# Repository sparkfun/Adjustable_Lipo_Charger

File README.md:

SparkFun Adjustable LiPo Charger
============================================

[*Adjustable LiPo Charger (PRT-14380)*](https://www.sparkfun.com/products/14380)

The Adjustable LiPo Charger will charge any single cell Lithium Ion (Li-Ion) or Lithium Polymer (LiPo) battery with a maximum current of 500mA. Simply plug in a micro B USB cable or any power supply between 3.75-6VDC to one end, and your rechargeable lithium battery to the other end. Once the current has been set on the DIP switches you're ready to go to charge your battery in 100mA increments up to 500mA, or as low as 15mA using the custom charge rate by soldering in the appropriate resistor to R_PTH.

Repository Contents
-------------------

* **/Hardware** - All Eagle design files (.brd and .sch)
* **/Production** - Production panel files

Documentation
-------------------

* [Adjustable LiPo Charger Hookup Guide ](https://learn.sparkfun.com/tutorials/adjustable-lipo-charger-hookup-guide)

License Information
-------------------
This product is _**open source**_! 

Please review the LICENSE.md file for license information. 

If you have any questions or concerns on licensing, please contact techsupport@sparkfun.com.

Distributed as-is; no warranty is given.

- Your friends at SparkFun.

All other code is open source so please feel free to do anything you want with it; you buy me a beer if you use this and we meet someday ([Beerware license](http://en.wikipedia.org/wiki/Beerware)).

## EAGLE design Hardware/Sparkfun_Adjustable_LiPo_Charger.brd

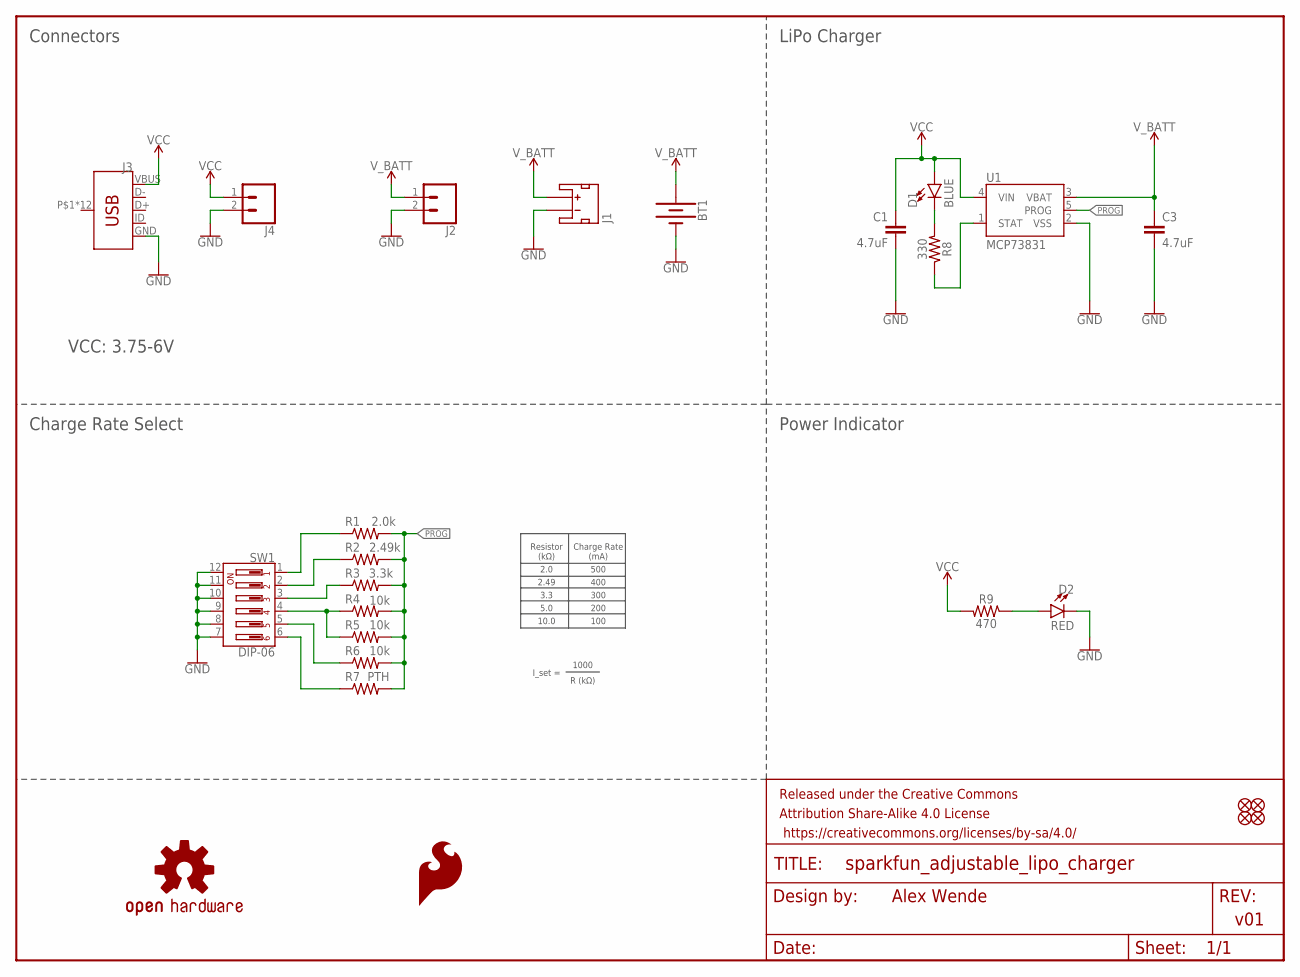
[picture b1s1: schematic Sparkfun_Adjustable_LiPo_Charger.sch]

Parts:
BT1: BATTERY-24.5MM_SMD; BATTCON_24.5MM_SMD
C1, C3: 4.7uF; 0603
D1: BLUE; LED-0603
D2: RED; LED-0603
FD1, FD2, FD3, FD4: FIDUCIALUFIDUCIAL; FIDUCIAL-MICRO
FRAME1: FRAME-LETTER; CREATIVE_COMMONS
J1: JST_2MM_MALE; JST-2-SMD
J2, J4: CONN_021X02_NO_SILK; 1X02_NO_SILK
J3: USB_MICRO-B_HALF_PTH; USB-MICROB-PTH
LOGO1: SFE_LOGO_FLAME.1_INCH; SFE_LOGO_FLAME_.1
LOGO2: OSHW-LOGOS; OSHW-LOGO-S
R1: 2.0k; 0603
R2: 2.49k; 0603
R3: 3.3k; 0603
R4, R5, R6: 10k; 0603
R7: PTH; AXIAL-0.3
R8: 330; 0603
R9: 470; 0603
SW1: DIP-06; DIPSWITCH-06-SMD
U1: MCP73831; SOT23-5

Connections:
GND: BT1.2 (-), C1.2, C3.2, D2.C, J1.1 (-), J2.2, J3.GND, J4.2, SW1.7, SW1.8, SW1.9, SW1.10, SW1.11, SW1.12, U1.2 (VSS)
unnamed: R8.1, U1.1 (STAT)
unnamed: R1.1, SW1.1
unnamed: R2.1, SW1.2
unnamed: R3.1, SW1.3
unnamed: R4.1, R5.1, SW1.4
unnamed: R6.1, SW1.5
unnamed: R7.P$1 (1), SW1.6
unnamed: D1.C, R8.2
unnamed: D2.A, R9.1
PROG: R1.2, R2.2, R3.2, R4.2, R5.2, R6.2, R7.P$2 (2), U1.5 (PROG)
VCC: C1.1, D1.A, J3.VBUS, J4.1, R9.2, U1.4 (VIN)
V_BATT: BT1.3 (+), C3.1, J1.2 (+), J2.1, U1.3 (VBAT)

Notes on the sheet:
Alex Wende
v01
Connectors
Charge Rate Select
Resistor (kΩ)
Charge Rate (mA)
2.0
2.49
3.3
5.0
10.0
500
400
300
200
100
I_set =
1000
R (kΩ)
LiPo Charger
VCC: 3.75-6V
Power Indicator

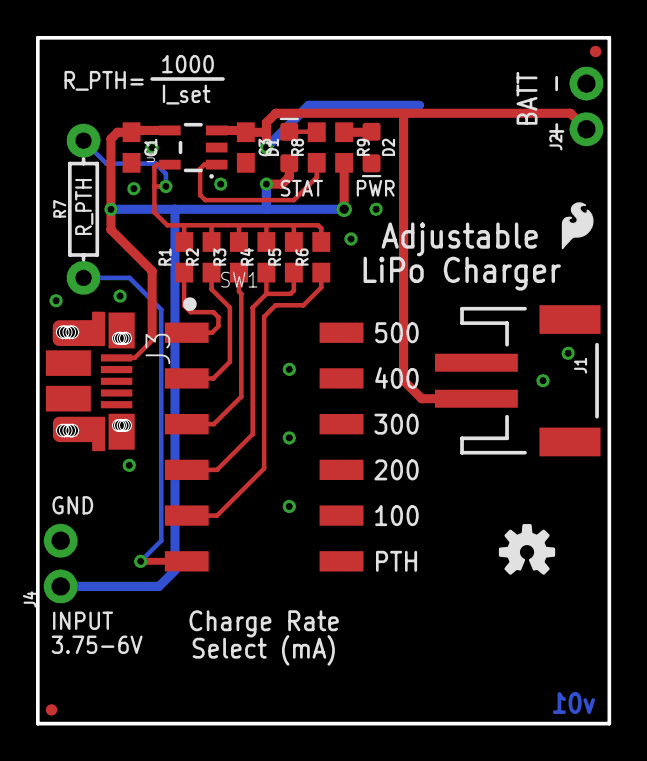
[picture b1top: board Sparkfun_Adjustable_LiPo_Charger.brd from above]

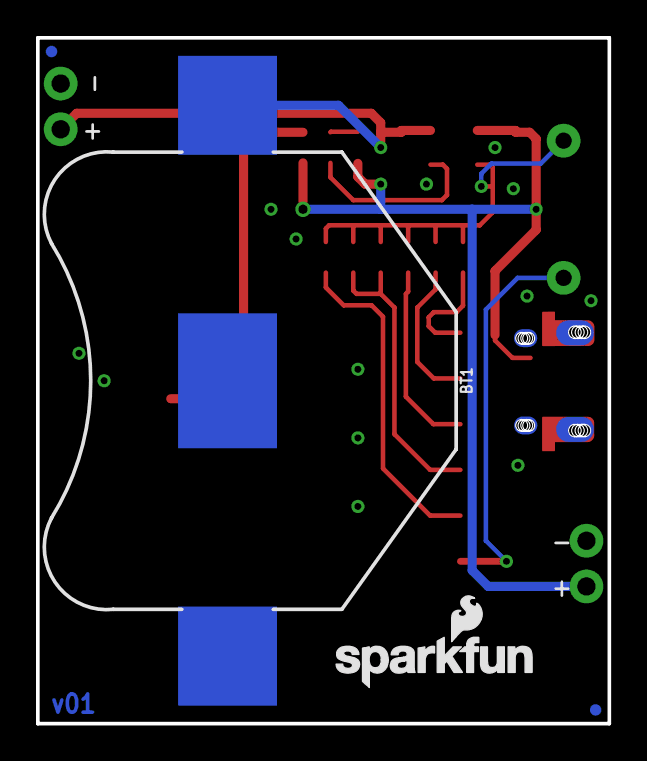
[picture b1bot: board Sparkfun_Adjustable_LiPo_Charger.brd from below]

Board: 2 copper layers, 31.8 x 38.1 mm, 28 parts (4 on the bottom side), 13 nets.

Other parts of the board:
U$1: SFE_LOGO_NAME_FLAME_.1

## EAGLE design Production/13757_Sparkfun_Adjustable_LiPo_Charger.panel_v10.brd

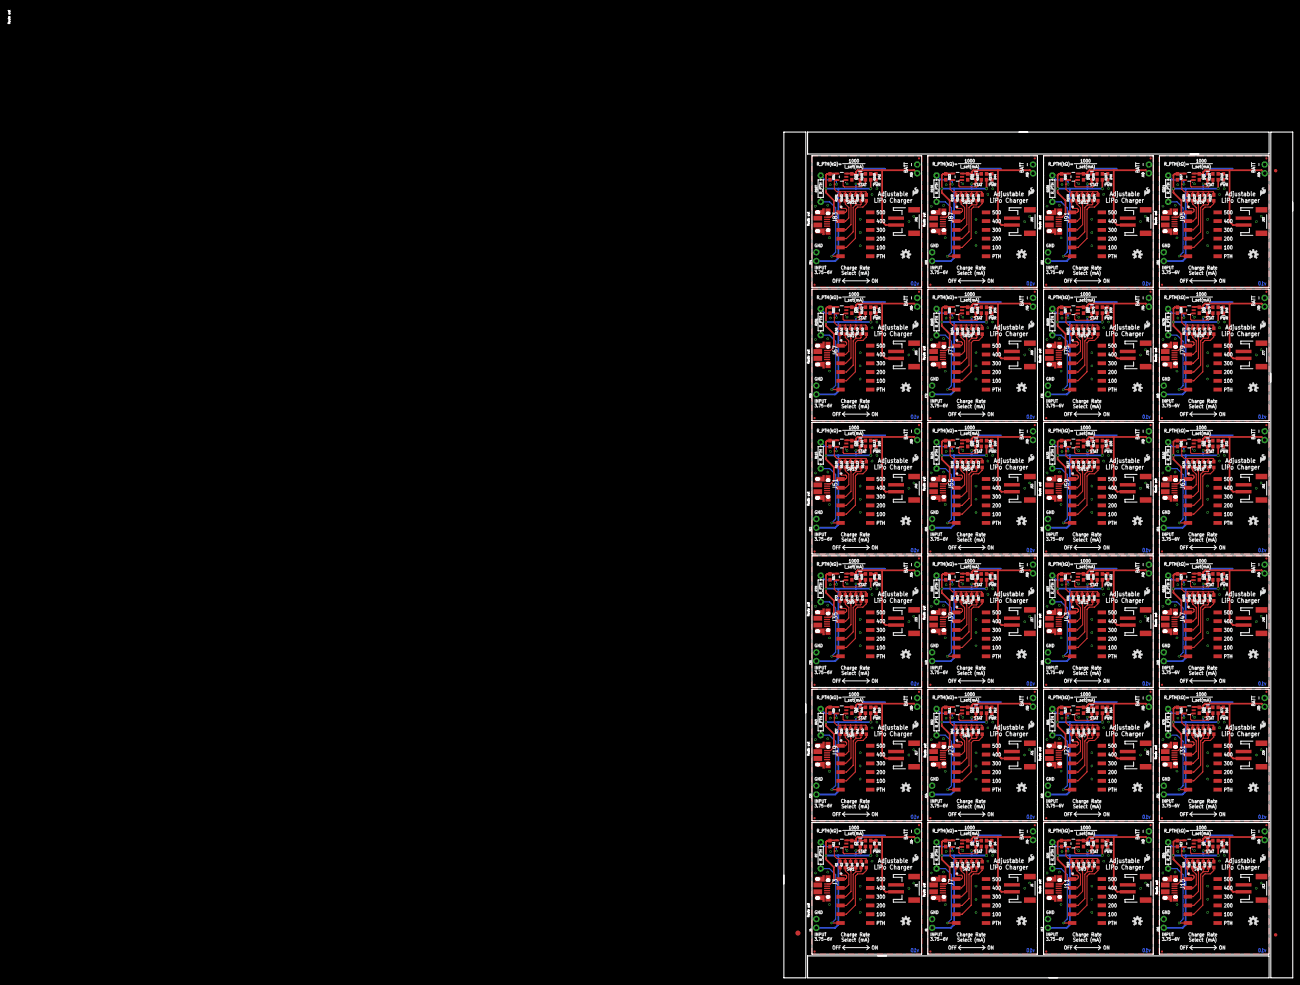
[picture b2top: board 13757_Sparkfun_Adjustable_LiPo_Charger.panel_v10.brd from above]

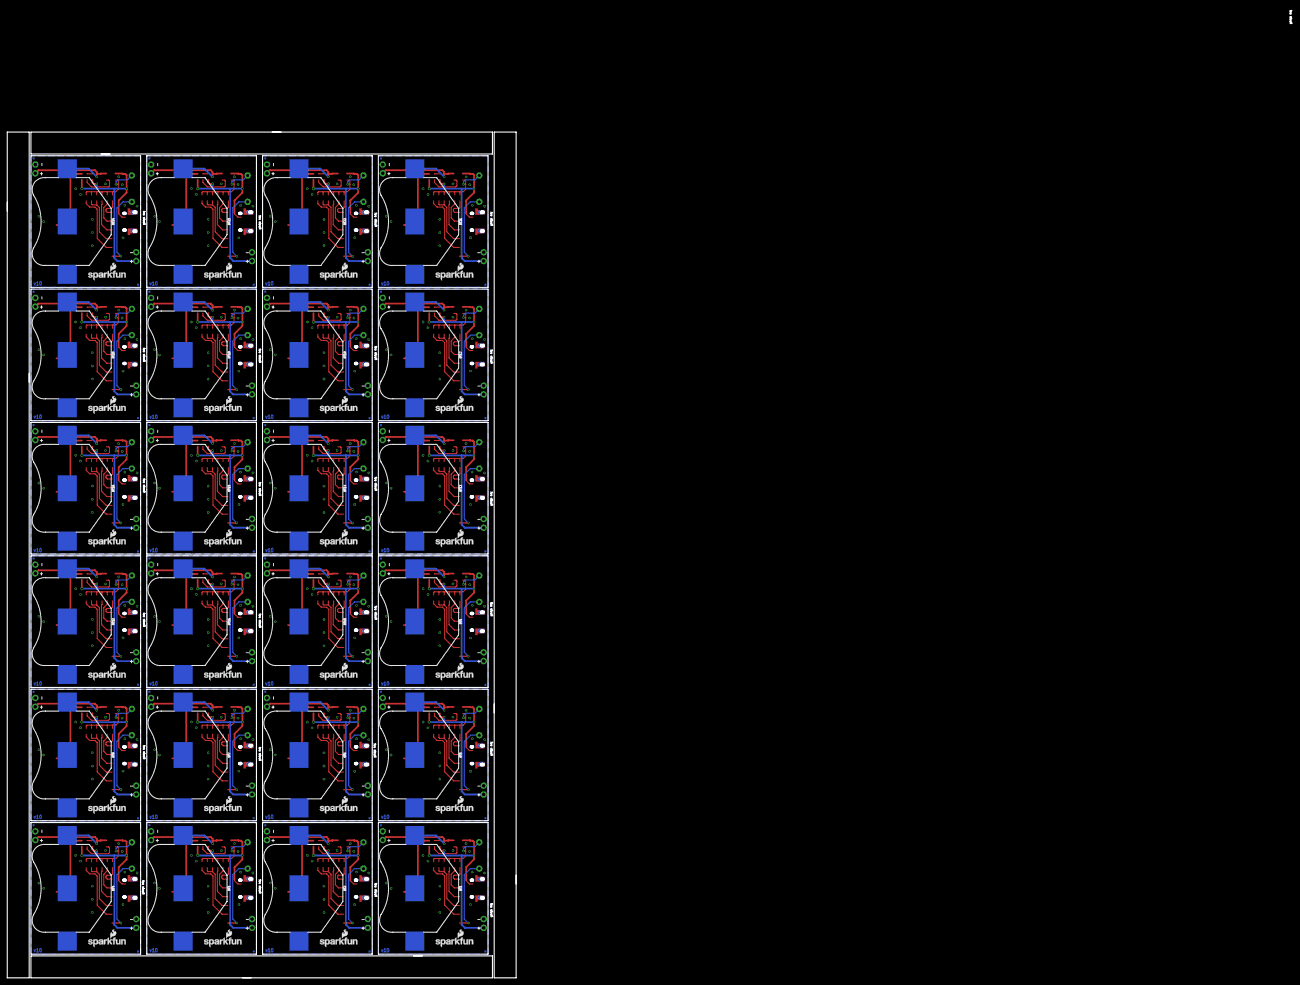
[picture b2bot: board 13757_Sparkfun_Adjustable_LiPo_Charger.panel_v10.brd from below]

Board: 2 copper layers, 372.2 x 281.0 mm, 651 parts (96 on the bottom side), 312 nets.

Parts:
BT1, BT2, BT3, BT4, BT5, BT6, BT7, BT8, BT9, BT10, BT11, BT12, BT13, BT14, BT15, BT16, BT17, BT18, BT19, BT20, BT21, BT22, BT23, BT24: BATTCON_24.5MM_SMD
C1, C2, C3, C4, C5, C6, C7, C8, C9, C10, C11, C12, C13, C14, C15, C16, C17, C18, C19, C20, C21, C22, C23, C24, C25, C26, C27, C28, C29, C30, C31, C32, C33, C34, C35, C36, C37, C38, C39, C40, C41, C42, C43, C44, C45, C46, C47, C48: 4.7uF; 0603
D1, D3, D5, D7, D9, D11, D13, D15, D17, D19, D21, D23, D25, D27, D29, D31, D33, D35, D37, D39, D41, D43, D45, D47: BLUE; LED-0603
D2, D4, D6, D8, D10, D12, D14, D16, D18, D20, D22, D24, D26, D28, D30, D32, D34, D36, D38, D40, D42, D44, D46, D48: RED; LED-0603
E$1: FIDUCIAL-1.5X3
E$7, E$8: FIDUCIAL-1X2
FD1, FD2, FD3, FD4, FD5, FD6, FD7, FD8, FD9, FD10, FD11, FD12, FD13, FD14, FD15, FD16, FD17, FD18, FD19, FD20, FD21, FD22, FD23, FD24, FD25, FD26, FD27, FD28, FD29, FD30, FD31, FD32, FD33, FD34, FD35, FD36, FD37, FD38, FD39, FD40, FD41, FD42, FD43, FD44, FD45, FD46, FD47, FD48, FD49, FD50, FD51, FD52, FD53, FD54, FD55, FD56, FD57, FD58, FD59, FD60, FD61, FD62, FD63, FD64, FD65, FD66, FD67, FD68, FD69, FD70, FD71, FD72, FD73, FD74, FD75, FD76, FD77, FD78, FD79, FD80, FD81, FD82, FD83, FD84, FD85, FD86, FD87, FD88, FD89, FD90, FD91, FD92, FD93, FD94, FD95, FD96: FIDUCIALUFIDUCIAL; FIDUCIAL-MICRO
J1, J5, J9, J13, J17, J21, J25, J29, J33, J37, J41, J45, J49, J53, J57, J61, J65, J69, J73, J77, J81, J85, J89, J93: JST-2-SMD
J2, J4, J6, J8, J10, J12, J14, J16, J18, J20, J22, J24, J26, J28, J30, J32, J34, J36, J38, J40, J42, J44, J46, J48, J50, J52, J54, J56, J58, J60, J62, J64, J66, J68, J70, J72, J74, J76, J78, J80, J82, J84, J86, J88, J90, J92, J94, J96: 1X02_NO_SILK
J3, J7, J11, J15, J19, J23, J27, J31, J35, J39, J43, J47, J51, J55, J59, J63, J67, J71, J75, J79, J83, J87, J91, J95: USB-MICROB-PTH
LOGO1, LOGO3, LOGO5, LOGO7, LOGO9, LOGO11, LOGO13, LOGO15, LOGO17, LOGO19, LOGO21, LOGO23, LOGO25, LOGO27, LOGO29, LOGO31, LOGO33, LOGO35, LOGO37, LOGO39, LOGO41, LOGO43, LOGO45, LOGO47: SFE_LOGO_FLAME.1_INCH; SFE_LOGO_FLAME_.1
LOGO2, LOGO4, LOGO6, LOGO8, LOGO10, LOGO12, LOGO14, LOGO16, LOGO18, LOGO20, LOGO22, LOGO24, LOGO26, LOGO28, LOGO30, LOGO32, LOGO34, LOGO36, LOGO38, LOGO40, LOGO42, LOGO44, LOGO46, LOGO48: OSHW-LOGOS; OSHW-LOGO-S
R1, R10, R19, R28, R37, R46, R55, R64, R73, R82, R91, R100, R109, R118, R127, R136, R145, R154, R163, R172, R181, R190, R199, R208: 2.0k; 0603
R2, R11, R20, R29, R38, R47, R56, R65, R74, R83, R92, R101, R110, R119, R128, R137, R146, R155, R164, R173, R182, R191, R200, R209: 2.49k; 0603
R3, R12, R21, R30, R39, R48, R57, R66, R75, R84, R93, R102, R111, R120, R129, R138, R147, R156, R165, R174, R183, R192, R201, R210: 3.3k; 0603
R4, R5, R6, R13, R14, R15, R22, R23, R24, R31, R32, R33, R40, R41, R42, R49, R50, R51, R58, R59, R60, R67, R68, R69, R76, R77, R78, R85, R86, R87, R94, R95, R96, R103, R104, R105, R112, R113, R114, R121, R122, R123, R130, R131, R132, R139, R140, R141, R148, R149, R150, R157, R158, R159, R166, R167, R168, R175, R176, R177, R184, R185, R186, R193, R194, R195, R202, R203, R204, R211, R212, R213: 10k; 0603
R7, R16, R25, R34, R43, R52, R61, R70, R79, R88, R97, R106, R115, R124, R133, R142, R151, R160, R169, R178, R187, R196, R205, R214: PTH; AXIAL-0.3
R8, R17, R26, R35, R44, R53, R62, R71, R80, R89, R98, R107, R116, R125, R134, R143, R152, R161, R170, R179, R188, R197, R206, R215: 330; 0603
R9, R18, R27, R36, R45, R54, R63, R72, R81, R90, R99, R108, R117, R126, R135, R144, R153, R162, R171, R180, R189, R198, R207, R216: 470; 0603
SW1, SW2, SW3, SW4, SW5, SW6, SW7, SW8, SW9, SW10, SW11, SW12, SW13, SW14, SW15, SW16, SW17, SW18, SW19, SW20, SW21, SW22, SW23, SW24: DIP-06; DIPSWITCH-06-SMD
U1, U2, U3, U4, U5, U6, U7, U8, U9, U10, U11, U12, U13, U14, U15, U16, U17, U18, U19, U20, U21, U22, U23, U24: MCP73831; SOT23-5
U$1, U$2, U$3, U$4, U$5, U$6, U$7, U$8, U$9, U$10, U$11, U$12, U$13, U$14, U$15, U$16, U$17, U$18, U$19, U$20, U$21, U$22, U$23, U$24: SFE_LOGO_NAME_FLAME_.1

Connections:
GND: BT1.2, C1.2, C3.2, D2.C, J1.1, J2.2, J3.GND, J4.2, SW1.7, SW1.8, SW1.9, SW1.10, SW1.11, SW1.12, U1.2
GND1: BT2.2, C2.2, C4.2, D4.C, J5.1, J6.2, J7.GND, J8.2, SW2.7, SW2.8, SW2.9, SW2.10, SW2.11, SW2.12, U2.2
GND2: BT3.2, C5.2, C6.2, D6.C, J9.1, J10.2, J11.GND, J12.2, SW3.7, SW3.8, SW3.9, SW3.10, SW3.11, SW3.12, U3.2
GND3: BT4.2, C7.2, C8.2, D8.C, J13.1, J14.2, J15.GND, J16.2, SW4.7, SW4.8, SW4.9, SW4.10, SW4.11, SW4.12, U4.2
GND4: BT5.2, C9.2, C10.2, D10.C, J17.1, J18.2, J19.GND, J20.2, SW5.7, SW5.8, SW5.9, SW5.10, SW5.11, SW5.12, U5.2
GND5: BT6.2, C11.2, C12.2, D12.C, J21.1, J22.2, J23.GND, J24.2, SW6.7, SW6.8, SW6.9, SW6.10, SW6.11, SW6.12, U6.2
GND6: BT7.2, C13.2, C14.2, D14.C, J25.1, J26.2, J27.GND, J28.2, SW7.7, SW7.8, SW7.9, SW7.10, SW7.11, SW7.12, U7.2
GND7: BT8.2, C15.2, C16.2, D16.C, J29.1, J30.2, J31.GND, J32.2, SW8.7, SW8.8, SW8.9, SW8.10, SW8.11, SW8.12, U8.2
GND8: BT9.2, C17.2, C18.2, D18.C, J33.1, J34.2, J35.GND, J36.2, SW9.7, SW9.8, SW9.9, SW9.10, SW9.11, SW9.12, U9.2
GND9: BT10.2, C19.2, C20.2, D20.C, J37.1, J38.2, J39.GND, J40.2, SW10.7, SW10.8, SW10.9, SW10.10, SW10.11, SW10.12, U10.2
GND10: BT11.2, C21.2, C22.2, D22.C, J41.1, J42.2, J43.GND, J44.2, SW11.7, SW11.8, SW11.9, SW11.10, SW11.11, SW11.12, U11.2
GND11: BT12.2, C23.2, C24.2, D24.C, J45.1, J46.2, J47.GND, J48.2, SW12.7, SW12.8, SW12.9, SW12.10, SW12.11, SW12.12, U12.2
GND12: BT13.2, C25.2, C26.2, D26.C, J49.1, J50.2, J51.GND, J52.2, SW13.7, SW13.8, SW13.9, SW13.10, SW13.11, SW13.12, U13.2
GND13: BT14.2, C27.2, C28.2, D28.C, J53.1, J54.2, J55.GND, J56.2, SW14.7, SW14.8, SW14.9, SW14.10, SW14.11, SW14.12, U14.2
GND14: BT15.2, C29.2, C30.2, D30.C, J57.1, J58.2, J59.GND, J60.2, SW15.7, SW15.8, SW15.9, SW15.10, SW15.11, SW15.12, U15.2
GND15: BT16.2, C31.2, C32.2, D32.C, J61.1, J62.2, J63.GND, J64.2, SW16.7, SW16.8, SW16.9, SW16.10, SW16.11, SW16.12, U16.2
GND16: BT17.2, C33.2, C34.2, D34.C, J65.1, J66.2, J67.GND, J68.2, SW17.7, SW17.8, SW17.9, SW17.10, SW17.11, SW17.12, U17.2
GND17: BT18.2, C35.2, C36.2, D36.C, J69.1, J70.2, J71.GND, J72.2, SW18.7, SW18.8, SW18.9, SW18.10, SW18.11, SW18.12, U18.2
GND18: BT19.2, C37.2, C38.2, D38.C, J73.1, J74.2, J75.GND, J76.2, SW19.7, SW19.8, SW19.9, SW19.10, SW19.11, SW19.12, U19.2
GND19: BT20.2, C39.2, C40.2, D40.C, J77.1, J78.2, J79.GND, J80.2, SW20.7, SW20.8, SW20.9, SW20.10, SW20.11, SW20.12, U20.2
GND20: BT21.2, C41.2, C42.2, D42.C, J81.1, J82.2, J83.GND, J84.2, SW21.7, SW21.8, SW21.9, SW21.10, SW21.11, SW21.12, U21.2
GND21: BT22.2, C43.2, C44.2, D44.C, J85.1, J86.2, J87.GND, J88.2, SW22.7, SW22.8, SW22.9, SW22.10, SW22.11, SW22.12, U22.2
GND22: BT23.2, C45.2, C46.2, D46.C, J89.1, J90.2, J91.GND, J92.2, SW23.7, SW23.8, SW23.9, SW23.10, SW23.11, SW23.12, U23.2
GND23: BT24.2, C47.2, C48.2, D48.C, J93.1, J94.2, J95.GND, J96.2, SW24.7, SW24.8, SW24.9, SW24.10, SW24.11, SW24.12, U24.2
unnamed: R8.1, U1.1
unnamed: R1.1, SW1.1
unnamed: R2.1, SW1.2
unnamed: R3.1, SW1.3
unnamed: R4.1, R5.1, SW1.4
unnamed: R6.1, SW1.5
unnamed: R7.P$1, SW1.6
unnamed: D1.C, R8.2
unnamed: R10.1, SW2.1
unnamed: R11.1, SW2.2
unnamed: R12.1, SW2.3
unnamed: D2.A, R9.1
unnamed: R13.1, R14.1, SW2.4
unnamed: R15.1, SW2.5
unnamed: R16.P$1, SW2.6
unnamed: R17.1, U2.1
unnamed: D4.A, R18.1
unnamed: D3.C, R17.2
unnamed: R19.1, SW3.1
unnamed: R20.1, SW3.2
unnamed: R21.1, SW3.3
unnamed: R22.1, R23.1, SW3.4
unnamed: R24.1, SW3.5
unnamed: R25.P$1, SW3.6
unnamed: R26.1, U3.1
unnamed: D6.A, R27.1
unnamed: D5.C, R26.2
unnamed: R28.1, SW4.1
unnamed: R29.1, SW4.2
unnamed: R30.1, SW4.3
unnamed: R31.1, R32.1, SW4.4
unnamed: R33.1, SW4.5
unnamed: R34.P$1, SW4.6
unnamed: R35.1, U4.1
unnamed: D8.A, R36.1
unnamed: D7.C, R35.2
unnamed: R37.1, SW5.1
unnamed: R38.1, SW5.2
unnamed: R39.1, SW5.3
unnamed: R40.1, R41.1, SW5.4
unnamed: R42.1, SW5.5
unnamed: R43.P$1, SW5.6
unnamed: R44.1, U5.1
unnamed: D10.A, R45.1
unnamed: D9.C, R44.2
unnamed: R46.1, SW6.1
unnamed: R47.1, SW6.2
unnamed: R48.1, SW6.3
unnamed: R49.1, R50.1, SW6.4
unnamed: R51.1, SW6.5
unnamed: R52.P$1, SW6.6
unnamed: R53.1, U6.1
unnamed: D12.A, R54.1
unnamed: D11.C, R53.2
unnamed: R55.1, SW7.1
unnamed: R56.1, SW7.2
unnamed: R57.1, SW7.3
unnamed: R58.1, R59.1, SW7.4
unnamed: R60.1, SW7.5
unnamed: R61.P$1, SW7.6
unnamed: R62.1, U7.1
unnamed: D14.A, R63.1
unnamed: D13.C, R62.2
unnamed: R64.1, SW8.1
unnamed: R65.1, SW8.2
unnamed: R66.1, SW8.3
unnamed: R67.1, R68.1, SW8.4
unnamed: R69.1, SW8.5
unnamed: R70.P$1, SW8.6
unnamed: R71.1, U8.1
unnamed: D16.A, R72.1
unnamed: D15.C, R71.2
unnamed: R73.1, SW9.1
unnamed: R74.1, SW9.2
unnamed: R75.1, SW9.3
unnamed: R76.1, R77.1, SW9.4
unnamed: R78.1, SW9.5
unnamed: R79.P$1, SW9.6
unnamed: R80.1, U9.1
unnamed: D18.A, R81.1
unnamed: D17.C, R80.2
unnamed: R82.1, SW10.1
unnamed: R83.1, SW10.2
unnamed: R84.1, SW10.3
unnamed: R85.1, R86.1, SW10.4
unnamed: R87.1, SW10.5
unnamed: R88.P$1, SW10.6
unnamed: R89.1, U10.1
unnamed: D20.A, R90.1
unnamed: D19.C, R89.2
unnamed: R91.1, SW11.1
unnamed: R92.1, SW11.2
unnamed: R93.1, SW11.3
unnamed: R94.1, R95.1, SW11.4
unnamed: R96.1, SW11.5
unnamed: R97.P$1, SW11.6
unnamed: R98.1, U11.1
unnamed: D22.A, R99.1
unnamed: D21.C, R98.2
unnamed: R100.1, SW12.1
unnamed: R101.1, SW12.2
unnamed: R102.1, SW12.3
unnamed: R103.1, R104.1, SW12.4
unnamed: R105.1, SW12.5
unnamed: R106.P$1, SW12.6
unnamed: R107.1, U12.1
unnamed: D24.A, R108.1
unnamed: D23.C, R107.2
unnamed: R109.1, SW13.1
unnamed: R110.1, SW13.2
unnamed: R111.1, SW13.3
unnamed: R112.1, R113.1, SW13.4
unnamed: R114.1, SW13.5
unnamed: R115.P$1, SW13.6
unnamed: R116.1, U13.1
unnamed: D26.A, R117.1
unnamed: D25.C, R116.2
unnamed: R118.1, SW14.1
unnamed: R119.1, SW14.2
unnamed: R120.1, SW14.3
unnamed: R121.1, R122.1, SW14.4
unnamed: R123.1, SW14.5
unnamed: R124.P$1, SW14.6
unnamed: R125.1, U14.1
unnamed: D28.A, R126.1
unnamed: D27.C, R125.2
unnamed: R127.1, SW15.1
unnamed: R128.1, SW15.2
unnamed: R129.1, SW15.3
unnamed: R130.1, R131.1, SW15.4
unnamed: R132.1, SW15.5
unnamed: R133.P$1, SW15.6
unnamed: R134.1, U15.1
unnamed: D30.A, R135.1
unnamed: D29.C, R134.2
unnamed: R136.1, SW16.1
unnamed: R137.1, SW16.2
unnamed: R138.1, SW16.3
unnamed: R139.1, R140.1, SW16.4
unnamed: R141.1, SW16.5
unnamed: R142.P$1, SW16.6
unnamed: R143.1, U16.1
unnamed: D32.A, R144.1
unnamed: D31.C, R143.2
unnamed: R145.1, SW17.1
unnamed: R146.1, SW17.2
unnamed: R147.1, SW17.3
unnamed: R148.1, R149.1, SW17.4
unnamed: R150.1, SW17.5
unnamed: R151.P$1, SW17.6
unnamed: R152.1, U17.1
unnamed: D34.A, R153.1
unnamed: D33.C, R152.2
unnamed: R154.1, SW18.1
unnamed: R155.1, SW18.2
unnamed: R156.1, SW18.3
unnamed: R157.1, R158.1, SW18.4
unnamed: R159.1, SW18.5
unnamed: R160.P$1, SW18.6
unnamed: R161.1, U18.1
unnamed: D36.A, R162.1
unnamed: D35.C, R161.2
unnamed: R163.1, SW19.1
unnamed: R164.1, SW19.2
unnamed: R165.1, SW19.3
unnamed: R166.1, R167.1, SW19.4
unnamed: R168.1, SW19.5
unnamed: R169.P$1, SW19.6
unnamed: R170.1, U19.1
unnamed: D38.A, R171.1
unnamed: D37.C, R170.2
unnamed: R172.1, SW20.1
unnamed: R173.1, SW20.2
unnamed: R174.1, SW20.3
unnamed: R175.1, R176.1, SW20.4
unnamed: R177.1, SW20.5
unnamed: R178.P$1, SW20.6
unnamed: R179.1, U20.1
unnamed: D40.A, R180.1
unnamed: D39.C, R179.2
unnamed: R181.1, SW21.1
unnamed: R182.1, SW21.2
unnamed: R183.1, SW21.3
unnamed: R184.1, R185.1, SW21.4
unnamed: R186.1, SW21.5
unnamed: R187.P$1, SW21.6
unnamed: R188.1, U21.1
unnamed: D42.A, R189.1
unnamed: D41.C, R188.2
unnamed: R190.1, SW22.1
unnamed: R191.1, SW22.2
unnamed: R192.1, SW22.3
unnamed: R193.1, R194.1, SW22.4
unnamed: R195.1, SW22.5
unnamed: R196.P$1, SW22.6
unnamed: R197.1, U22.1
unnamed: D44.A, R198.1
unnamed: D43.C, R197.2
unnamed: R199.1, SW23.1
unnamed: R200.1, SW23.2
unnamed: R201.1, SW23.3
unnamed: R202.1, R203.1, SW23.4
unnamed: R204.1, SW23.5
unnamed: R205.P$1, SW23.6
unnamed: R206.1, U23.1
unnamed: D46.A, R207.1
unnamed: D45.C, R206.2
unnamed: R208.1, SW24.1
unnamed: R209.1, SW24.2
unnamed: R210.1, SW24.3
unnamed: R211.1, R212.1, SW24.4
unnamed: R213.1, SW24.5
unnamed: R214.P$1, SW24.6
unnamed: R215.1, U24.1
unnamed: D48.A, R216.1
unnamed: D47.C, R215.2
PROG: R1.2, R2.2, R3.2, R4.2, R5.2, R6.2, R7.P$2, U1.5
PROG1: R10.2, R11.2, R12.2, R13.2, R14.2, R15.2, R16.P$2, U2.5
PROG2: R19.2, R20.2, R21.2, R22.2, R23.2, R24.2, R25.P$2, U3.5
PROG3: R28.2, R29.2, R30.2, R31.2, R32.2, R33.2, R34.P$2, U4.5
PROG4: R37.2, R38.2, R39.2, R40.2, R41.2, R42.2, R43.P$2, U5.5
PROG5: R46.2, R47.2, R48.2, R49.2, R50.2, R51.2, R52.P$2, U6.5
PROG6: R55.2, R56.2, R57.2, R58.2, R59.2, R60.2, R61.P$2, U7.5
PROG7: R64.2, R65.2, R66.2, R67.2, R68.2, R69.2, R70.P$2, U8.5
PROG8: R73.2, R74.2, R75.2, R76.2, R77.2, R78.2, R79.P$2, U9.5
PROG9: R82.2, R83.2, R84.2, R85.2, R86.2, R87.2, R88.P$2, U10.5
PROG10: R91.2, R92.2, R93.2, R94.2, R95.2, R96.2, R97.P$2, U11.5
PROG11: R100.2, R101.2, R102.2, R103.2, R104.2, R105.2, R106.P$2, U12.5
PROG12: R109.2, R110.2, R111.2, R112.2, R113.2, R114.2, R115.P$2, U13.5
PROG13: R118.2, R119.2, R120.2, R121.2, R122.2, R123.2, R124.P$2, U14.5
PROG14: R127.2, R128.2, R129.2, R130.2, R131.2, R132.2, R133.P$2, U15.5
PROG15: R136.2, R137.2, R138.2, R139.2, R140.2, R141.2, R142.P$2, U16.5
PROG16: R145.2, R146.2, R147.2, R148.2, R149.2, R150.2, R151.P$2, U17.5
PROG17: R154.2, R155.2, R156.2, R157.2, R158.2, R159.2, R160.P$2, U18.5
PROG18: R163.2, R164.2, R165.2, R166.2, R167.2, R168.2, R169.P$2, U19.5
PROG19: R172.2, R173.2, R174.2, R175.2, R176.2, R177.2, R178.P$2, U20.5
PROG20: R181.2, R182.2, R183.2, R184.2, R185.2, R186.2, R187.P$2, U21.5
PROG21: R190.2, R191.2, R192.2, R193.2, R194.2, R195.2, R196.P$2, U22.5
PROG22: R199.2, R200.2, R201.2, R202.2, R203.2, R204.2, R205.P$2, U23.5
PROG23: R208.2, R209.2, R210.2, R211.2, R212.2, R213.2, R214.P$2, U24.5
VCC: C1.1, D1.A, J3.VBUS, J4.1, R9.2, U1.4
VCC1: C2.1, D3.A, J7.VBUS, J8.1, R18.2, U2.4
VCC2: C5.1, D5.A, J11.VBUS, J12.1, R27.2, U3.4
VCC3: C7.1, D7.A, J15.VBUS, J16.1, R36.2, U4.4
VCC4: C9.1, D9.A, J19.VBUS, J20.1, R45.2, U5.4
VCC5: C11.1, D11.A, J23.VBUS, J24.1, R54.2, U6.4
VCC6: C13.1, D13.A, J27.VBUS, J28.1, R63.2, U7.4
VCC7: C15.1, D15.A, J31.VBUS, J32.1, R72.2, U8.4
VCC8: C17.1, D17.A, J35.VBUS, J36.1, R81.2, U9.4
VCC9: C19.1, D19.A, J39.VBUS, J40.1, R90.2, U10.4
VCC10: C21.1, D21.A, J43.VBUS, J44.1, R99.2, U11.4
VCC11: C23.1, D23.A, J47.VBUS, J48.1, R108.2, U12.4
VCC12: C25.1, D25.A, J51.VBUS, J52.1, R117.2, U13.4
VCC13: C27.1, D27.A, J55.VBUS, J56.1, R126.2, U14.4
VCC14: C29.1, D29.A, J59.VBUS, J60.1, R135.2, U15.4
VCC15: C31.1, D31.A, J63.VBUS, J64.1, R144.2, U16.4
VCC16: C33.1, D33.A, J67.VBUS, J68.1, R153.2, U17.4
VCC17: C35.1, D35.A, J71.VBUS, J72.1, R162.2, U18.4
VCC18: C37.1, D37.A, J75.VBUS, J76.1, R171.2, U19.4
VCC19: C39.1, D39.A, J79.VBUS, J80.1, R180.2, U20.4
VCC20: C41.1, D41.A, J83.VBUS, J84.1, R189.2, U21.4
VCC21: C43.1, D43.A, J87.VBUS, J88.1, R198.2, U22.4
VCC22: C45.1, D45.A, J91.VBUS, J92.1, R207.2, U23.4
VCC23: C47.1, D47.A, J95.VBUS, J96.1, R216.2, U24.4
V_BATT: BT1.3, C3.1, J1.2, J2.1, U1.3
V_BATT1: BT2.3, C4.1, J5.2, J6.1, U2.3
V_BATT2: BT3.3, C6.1, J9.2, J10.1, U3.3
V_BATT3: BT4.3, C8.1, J13.2, J14.1, U4.3
V_BATT4: BT5.3, C10.1, J17.2, J18.1, U5.3
V_BATT5: BT6.3, C12.1, J21.2, J22.1, U6.3
V_BATT6: BT7.3, C14.1, J25.2, J26.1, U7.3
V_BATT7: BT8.3, C16.1, J29.2, J30.1, U8.3
V_BATT8: BT9.3, C18.1, J33.2, J34.1, U9.3
V_BATT9: BT10.3, C20.1, J37.2, J38.1, U10.3
V_BATT10: BT11.3, C22.1, J41.2, J42.1, U11.3
V_BATT11: BT12.3, C24.1, J45.2, J46.1, U12.3
V_BATT12: BT13.3, C26.1, J49.2, J50.1, U13.3
V_BATT13: BT14.3, C28.1, J53.2, J54.1, U14.3
V_BATT14: BT15.3, C30.1, J57.2, J58.1, U15.3
V_BATT15: BT16.3, C32.1, J61.2, J62.1, U16.3
V_BATT16: BT17.3, C34.1, J65.2, J66.1, U17.3
V_BATT17: BT18.3, C36.1, J69.2, J70.1, U18.3
V_BATT18: BT19.3, C38.1, J73.2, J74.1, U19.3
V_BATT19: BT20.3, C40.1, J77.2, J78.1, U20.3
V_BATT20: BT21.3, C42.1, J81.2, J82.1, U21.3
V_BATT21: BT22.3, C44.1, J85.2, J86.1, U22.3
V_BATT22: BT23.3, C46.1, J89.2, J90.1, U23.3
V_BATT23: BT24.3, C48.1, J93.2, J94.1, U24.3

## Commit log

2017-06-28 Added hardware
    Added the schematic and board files
2017-06-30 Design Review Changes
    Replaced PTH coin cell holder with SMD
2017-08-04 Proto Changes
    Fixed layout error of D1 to the correct orientation
2017-08-08 v10 changes
    - Added switch label to indicate on/off position.
    - Added units to charge rate equation
2017-08-14 panel
2017-09-29 Fixed Astetics in README
2017-09-29 Add Documentation and Standard SFE License
    Added Links for documentation and standard SparkFun license.
2017-09-29 Add Standard SFE License
2017-09-29 Create .gitattributes
    Add .gitattributes

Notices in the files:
parts and their libraries:
SparkFun-Batteries: Licensing: Creative Commons ShareAlike 4.0 International - https://creativecommons.org/licenses/by-sa/4.0
SparkFun-Aesthetics: Released under the Creative Commons Attribution Share-Alike 4.0 License
SparkFun-Aesthetics: https://creativecommons.org/licenses/by-sa/4.0
